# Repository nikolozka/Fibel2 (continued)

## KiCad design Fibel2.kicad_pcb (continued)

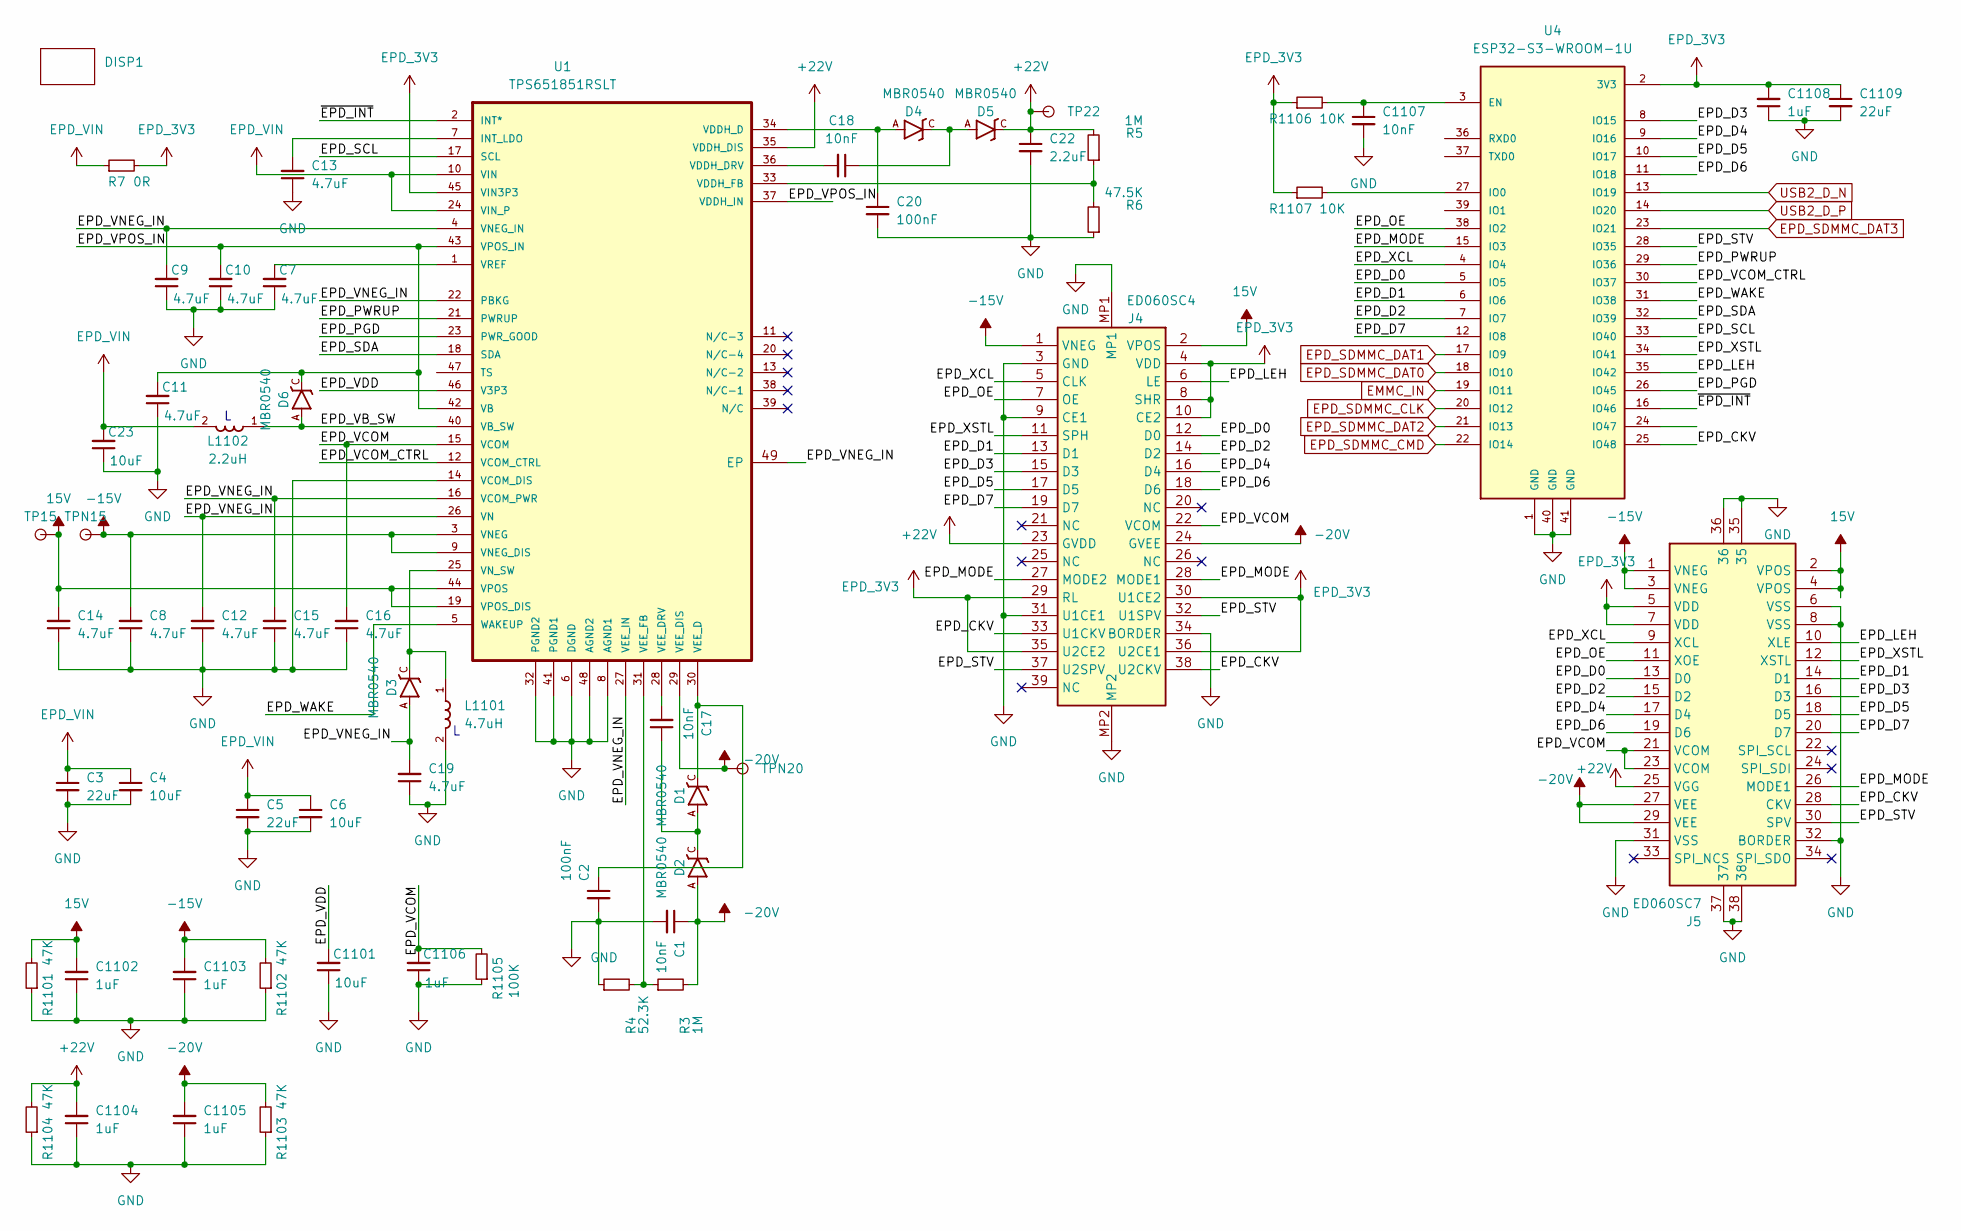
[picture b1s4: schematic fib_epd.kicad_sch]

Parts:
C1, C17, C18, C1107: 10nF; C_0402_1005Metric
C2, C20: 100nF; C_0402_1005Metric
C3, C5, C1109: 22uF; C_0805_2012Metric
C4, C6, C23: 10uF; C_0603_1608Metric
C7, C8, C9, C10, C11, C12, C13, C14, C15, C16, C19: 4.7uF; C_0402_1005Metric
C22: 2.2uF; C_0402_1005Metric
C1101: 10uF; C_0805_2012Metric
C1102, C1103, C1104, C1105, C1106, C1108: 1uF; C_0805_2012Metric
D1, D2, D3, D4, D5, D6: MBR0540; SOD-123
DISP1: 7.8 EInk
J4: ED060SC4; Mouser Part Number 798-FH26W39S03SHW60
J5: ED060SC7; Mouser Part Number 769-AXT334124
L1101: 4.7uH; IND_LQH5BPB4R7NT0L
L1102: 2.2uH; IND_LQH44PN4R7MP0L
R3, R5: 1M; R_0402_1005Metric
R4: 52.3K; R_0402_1005Metric
R6: 47.5K; R_0402_1005Metric
R7: 0R; R_0603_1608Metric
R1101, R1102, R1103, R1104: 47K; R_0402_1005Metric
R1105: 100K; R_0402_1005Metric
R1106, R1107: 10K; R_0402_1005Metric
TP15, TP22: TestPoint; TestPoint_Pad_D1.0mm
TPN15, TPN20: TestPoint; TestPoint_Pad_D1.0mm
U1: TPS651851RSLT; IC_TPS651851
U4: ESP32-S3-WROOM-1U; XCVR_ESP32-S3-WROOM-1U

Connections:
15V: C14.2, C1102.2, J4.2 (VPOS), J5.2 (VPOS), J5.4 (VPOS), R1101.2, TP15.1, U1.19 (VPOS_DIS), U1.44 (VPOS)
+22V: C22.1, C1104.2, D5.C, J4.23 (GVDD), J5.25 (VGG), R5.2, R1104.2, TP22.1, U1.35 (VDDH_DIS)
-15V: C8.2, C1103.2, J4.1 (VNEG), J5.1 (VNEG), J5.3 (VNEG), R1102.2, TPN15.1, U1.3 (VNEG), U1.9 (VNEG_DIS)
-20V: C1.1, C1105.2, D2.A, J4.24 (GVEE), J5.27 (VEE), J5.29 (VEE), R3.2, R1103.2, TPN20.1, U1.29 (VEE_DIS)
/EPD/EPD_CKV: J4.33 (U1CKV), J4.38 (U2CKV), J5.28 (CKV), U4.25 (IO48)
/EPD/EPD_D0: J4.12 (D0), J5.13 (D0), U4.5 (IO5)
/EPD/EPD_D1: J4.13 (D1), J5.14 (D1), U4.6 (IO6)
/EPD/EPD_D2: J4.14 (D2), J5.15 (D2), U4.7 (IO7)
/EPD/EPD_D3: J4.15 (D3), J5.16 (D3), U4.8 (IO15)
/EPD/EPD_D4: J4.16 (D4), J5.17 (D4), U4.9 (IO16)
/EPD/EPD_D5: J4.17 (D5), J5.18 (D5), U4.10 (IO17)
/EPD/EPD_D6: J4.18 (D6), J5.19 (D6), U4.11 (IO18)
/EPD/EPD_D7: J4.19 (D7), J5.20 (D7), U4.12 (IO8)
/EPD/EPD_LEH: J4.6 (LE), J5.10 (XLE), U4.35 (IO42)
/EPD/EPD_MODE: J4.27 (MODE2), J4.28 (MODE1), J5.26 (MODE1), U4.15 (IO3)
/EPD/EPD_OE: J4.7 (OE), J5.11 (XOE), U4.38 (IO2)
/EPD/EPD_PGD: U1.23 (PWR_GOOD), U4.26 (IO45)
/EPD/EPD_PWRUP: U1.21 (PWRUP), U4.29 (IO36)
/EPD/EPD_SCL: U1.17 (SCL), U4.33 (IO40)
/EPD/EPD_SDA: U1.18 (SDA), U4.32 (IO39)
/EPD/EPD_STV: J4.32 (U1SPV), J4.37 (U2SPV), J5.30 (SPV), U4.28 (IO35)
/EPD/EPD_VB_SW: D6.A, L1102.1, U1.40 (VB_SW)
/EPD/EPD_VCOM: C16.2, C1106.2, J4.22 (VCOM), J5.21 (VCOM), J5.23 (VCOM), R1105.2, U1.15 (VCOM)
/EPD/EPD_VCOM_CTRL: U1.12 (VCOM_CTRL), U4.30 (IO37)
/EPD/EPD_VDD: C1101.2, U1.46 (V3P3)
/EPD/EPD_VNEG_IN: C9.2, C12.2, C15.2, C19.2, D3.A, U1.4 (VNEG_IN), U1.16 (VCOM_PWR), U1.22 (PBKG), U1.26 (VN), U1.27 (VEE_IN), U1.49 (EP)
/EPD/EPD_VPOS_IN: C10.2, C11.2, D6.C, U1.37 (VDDH_IN), U1.42 (VB), U1.43 (VPOS_IN)
/EPD/EPD_WAKE: U1.5 (WAKEUP), U4.31 (IO38)
/EPD/EPD_XCL: J4.5 (CLK), J5.9 (XCL), U4.4 (IO4)
/EPD/EPD_XSTL: J4.11 (SPH), J5.12 (XSTL), U4.34 (IO41)
/EPD/~EPD_INT: U1.2 (INT*), U4.16 (IO46)
EMMC_IN: U4.19 (IO11); also elsewhere on the board
EPD_3V3: C1108.2, C1109.1, J4.4 (VDD), J4.8 (SHR), J4.10 (CE2), J4.29 (RL), J4.30 (U1CE2), J4.35 (U2CE2), J4.36 (U2CE1), J5.5 (VDD), J5.7 (VDD), R7.2, R1106.1, R1107.1, U1.45 (VIN3P3), U4.2 (3V3); also elsewhere on the board
EPD_SDMMC_CLK: U4.20 (IO12); also elsewhere on the board
EPD_SDMMC_CMD: U4.22 (IO14); also elsewhere on the board
EPD_SDMMC_DAT0: U4.18 (IO10); also elsewhere on the board
EPD_SDMMC_DAT1: U4.17 (IO9); also elsewhere on the board
EPD_SDMMC_DAT2: U4.21 (IO13); also elsewhere on the board
EPD_SDMMC_DAT3: U4.23 (IO21); also elsewhere on the board
EPD_VIN: C3.1, C4.1, C5.1, C6.1, C23.2, L1102.2, R7.1, U1.10 (VIN), U1.24 (VIN_P)
GND: C1.2, C2.2, C3.2, C4.2, C5.2, C6.2, C7.1, C8.1, C9.1, C10.1, C11.1, C12.1, C13.1, C14.1, C15.1, C16.1, C19.1, C20.2, C22.2, C23.1, C1101.1, C1102.1, C1103.1, C1104.1, C1105.1, C1106.1, C1107.2, C1108.1, C1109.2, J4.3 (GND), J4.9 (CE1), J4.31 (U1CE1), J4.34 (BORDER), J4.MP1, J4.MP2, J5.6 (VSS), J5.8 (VSS), J5.31 (VSS), J5.32 (BORDER), J5.35, J5.36, J5.37, J5.38, L1101.2, R4.1, R6.1, R1101.1, R1102.1, R1103.1, R1104.1, R1105.1, U1.6 (DGND), U1.8 (AGND1), U1.14 (VCOM_DIS), U1.32 (PGND2), U1.41 (PGND1), U1.48 (AGND2), U4.1 (GND), U4.40 (GND), U4.41 (GND); also elsewhere on the board
unnamed: C17.1, D1.A, D2.C
unnamed: C18.1, D4.C, D5.A
unnamed: C13.2, U1.7 (INT_LDO)
unnamed: C20.1, D4.A, U1.34 (VDDH_D)
unnamed: C18.2, U1.36 (VDDH_DRV)
unnamed: R5.1, R6.2, U1.33 (VDDH_FB)
unnamed: C2.1, D1.C, U1.30 (VEE_D)
unnamed: C17.2, U1.28 (VEE_DRV)
unnamed: R3.1, R4.2, U1.31 (VEE_FB)
unnamed: D3.C, L1101.1, U1.25 (VN_SW)
unnamed: C7.2, U1.1 (VREF)
unnamed: C1107.1, R1106.2, U4.3 (EN)
unnamed: R1107.2, U4.27 (IO0)
USB2_D_N: U4.13 (IO19); also elsewhere on the board
USB2_D_P: U4.14 (IO20); also elsewhere on the board

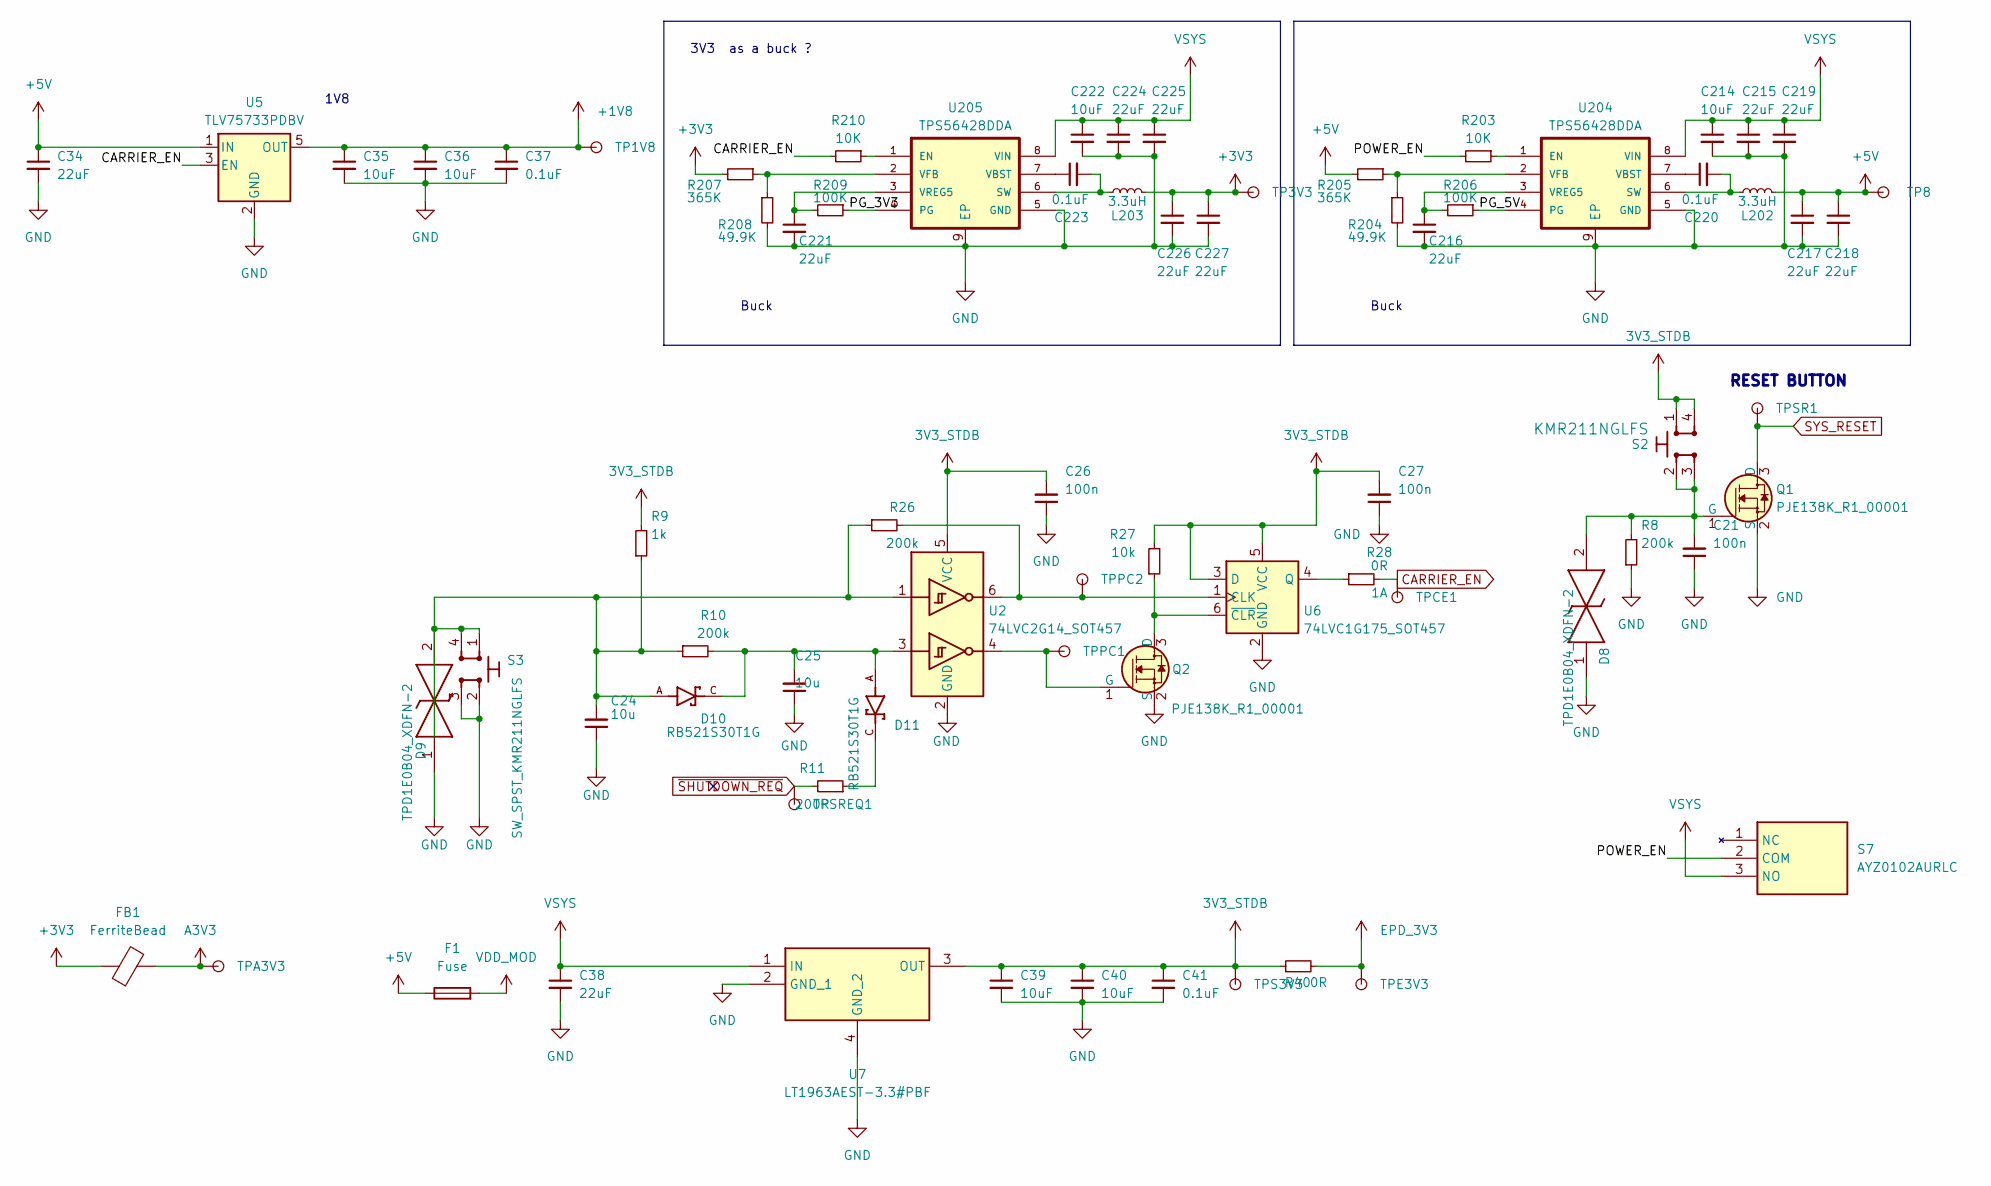
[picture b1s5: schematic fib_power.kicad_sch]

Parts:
C21, C26, C27: C_Small_Rota; C_0402_1005Metric; Voltage 50V; MPN GRM155R61H104KE14D
C24, C25: C_Small_Rota; C_0402_1005Metric; MPN CC0402MRX5R5BB106
C34, C38, C215, C216, C218, C219, C221, C224, C225, C227: 22uF; C_0805_2012Metric
C35, C36, C39, C40, C214, C222: 10uF; C_0603_1608Metric
C37, C41, C220, C223: 0.1uF; C_0402_1005Metric
C217, C226: 22uF; C_0603_1608Metric
D8, D9: TPD1E0B04_XDFN-2; TPD1E0B04DPYT; MPN TPD1E0B04DPYR; Mouser Part Number 595-TPD1E0B04DPYT
D10, D11: RB521S30T1G; MPN RB521S30T1G
F1: Fuse; Fuse_1206
FB1: FerriteBead; Ferrite_1206
L202, L203: 3.3uH; L_Coilcraft_XAL4030-XXX
Q1, Q2: PJE138K_2; SOT-523; MPN PJE138K_R1_00001
R8, R10, R26: R_Small_Rota; R_0402_1005Metric; Tolerance 1%; MPN CR0402-FX-2003GLF
R9: R_Small_Rota; R_0402_1005Metric; Tolerance 1%; MPN CR0402-FX-1001GLF
R11: R_Small_Rota; R_0402_1005Metric; Tolerance 1%; MPN CR0402-FX-2000GLF
R27: R_Small_Rota; R_0402_1005Metric; Tolerance 1%; MPN CR0402-FX-1002GLF
R28: R_Small_Rota; R_0402_1005Metric; MPN ERJ2GE0R00X
R40: 0R; R_0603_1608Metric
R203, R210: 10K; R_0402_1005Metric
R204, R208: 49.9K; R_0402_1005Metric
R205, R207: 365K; R_0402_1005Metric
R206, R209: 100K; R_0402_1005Metric
S2, S3: SW_SPST_KMR211NGLFS; KMR211NGLFS; MPN KMR211NGLFS
S7: AYZ0102AURLC; Mouser Part Number 611-AYZ0102AURLC
TP1V8, TP3V3, TP8: TestPoint; TestPoint_Pad_D1.0mm
TPA3V3: TestPoint; TestPoint_Pad_D1.0mm
TPCE1: TestPoint; TestPoint_Pad_D1.0mm
TPE3V3: TestPoint; TestPoint_Pad_D1.0mm
TPPC1, TPPC2: TestPoint; TestPoint_Pad_D1.0mm
TPS3V3: TestPoint; TestPoint_Pad_D1.0mm
TPSR1: TestPoint; TestPoint_Pad_D1.0mm
TPSREQ1: TestPoint; TestPoint_Pad_D1.0mm
U2: 74LVC2G14_SOT457; SOT-23-6; MPN 74LVC2G14GV,125
U5: TLV75733PDBV; SOT-23-5
U6: 74LVC1G175_SOT457; SOT-23-6; MPN 74LVC1G175GV,125
U7: LT1963AEST-3.3#PBF; SOT230P700X180-4N; Mouser Part Number 584-1963AEST-3.3PBF
U204, U205: TPS56428DDA

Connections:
3V3_STDB: C26.2, C27.2, C39.1, C40.1, C41.1, R9.2, R27.2, R40.1, S2.1, S2.4, TPS3V3.1, U2.5 (VCC), U6.3 (D), U6.5 (VCC), U7.3 (OUT); also elsewhere on the board
+1V8: C35.1, C36.1, C37.1, TP1V8.1, U5.5 (OUT); also elsewhere on the board
+3V3: C226.1, C227.1, FB1.1, L203.2, R207.2, TP3V3.1; also elsewhere on the board
+5V: C34.1, C217.1, C218.1, F1.1, L202.2, R205.2, TP8.1, U5.1 (IN); also elsewhere on the board
/Power/PG_3V3: R209.1, U205.4 (PG)
/Power/PG_5V: R206.1, U204.4 (PG)
/Power/POWER_EN: R203.2, S7.2 (COM)
A3V3: FB1.2, TPA3V3.1; also elsewhere on the board
CARRIER_EN: R28.2, R210.2, TPCE1.1, U5.3 (EN); also elsewhere on the board
EPD_3V3: R40.2, TPE3V3.1; also elsewhere on the board
GND: C21.1, C24.1, C25.1, C26.1, C27.1, C34.2, C35.2, C36.2, C37.2, C38.2, C39.2, C40.2, C41.2, C214.2, C215.2, C216.2, C217.2, C218.2, C219.2, C221.2, C222.2, C224.2, C225.2, C226.2, C227.2, D8.1, D9.1, Q1.2 (S), Q2.2 (S), R8.1, R204.2, R208.2, S3.2, S3.3, U2.2 (GND), U5.2 (GND), U6.2 (GND), U7.2 (GND_1), U7.4 (GND_2), U204.5 (GND), U204.9 (EP), U205.5 (GND), U205.9 (EP); also elsewhere on the board
unnamed: C24.2, D9.2, D10.A, R9.1, R10.1, R26.1, S3.1, S3.4, U2.1
unnamed: C25.2, D10.C, D11.A, R10.2, U2.3
unnamed: D11.C, R11.1
unnamed: C21.2, D8.2, Q1.1 (G), R8.2, S2.2, S2.3
unnamed: Q2.3 (D), R27.1, U6.6 (~CLR)
unnamed: Q2.1 (G), TPPC1.1, U2.4
unnamed: R26.2, TPPC2.1, U2.6, U6.1 (CLK)
unnamed: R28.1, U6.4 (Q)
unnamed: R203.1, U204.1 (EN)
unnamed: C220.2, L202.1, U204.6 (SW)
unnamed: C220.1, U204.7 (VBST)
unnamed: R204.1, R205.1, U204.2 (VFB)
unnamed: C216.1, R206.2, U204.3 (VREG5)
unnamed: R210.1, U205.1 (EN)
unnamed: C223.2, L203.1, U205.6 (SW)
unnamed: C223.1, U205.7 (VBST)
unnamed: R207.1, R208.1, U205.2 (VFB)
unnamed: C221.1, R209.2, U205.3 (VREG5)
SYS_RESET: Q1.3 (D), TPSR1.1; also elsewhere on the board
VDD_MOD: F1.2; also elsewhere on the board
VSYS: C38.1, C214.1, C215.1, C219.1, C222.1, C224.1, C225.1, S7.3 (NO), U7.1 (IN), U204.8 (VIN), U205.8 (VIN); also elsewhere on the board
~SHUTDOWN_REQ: R11.2, TPSREQ1.1; also elsewhere on the board

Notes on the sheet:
Buck
3V3 as a buck ?
1V8
RESET BUTTON

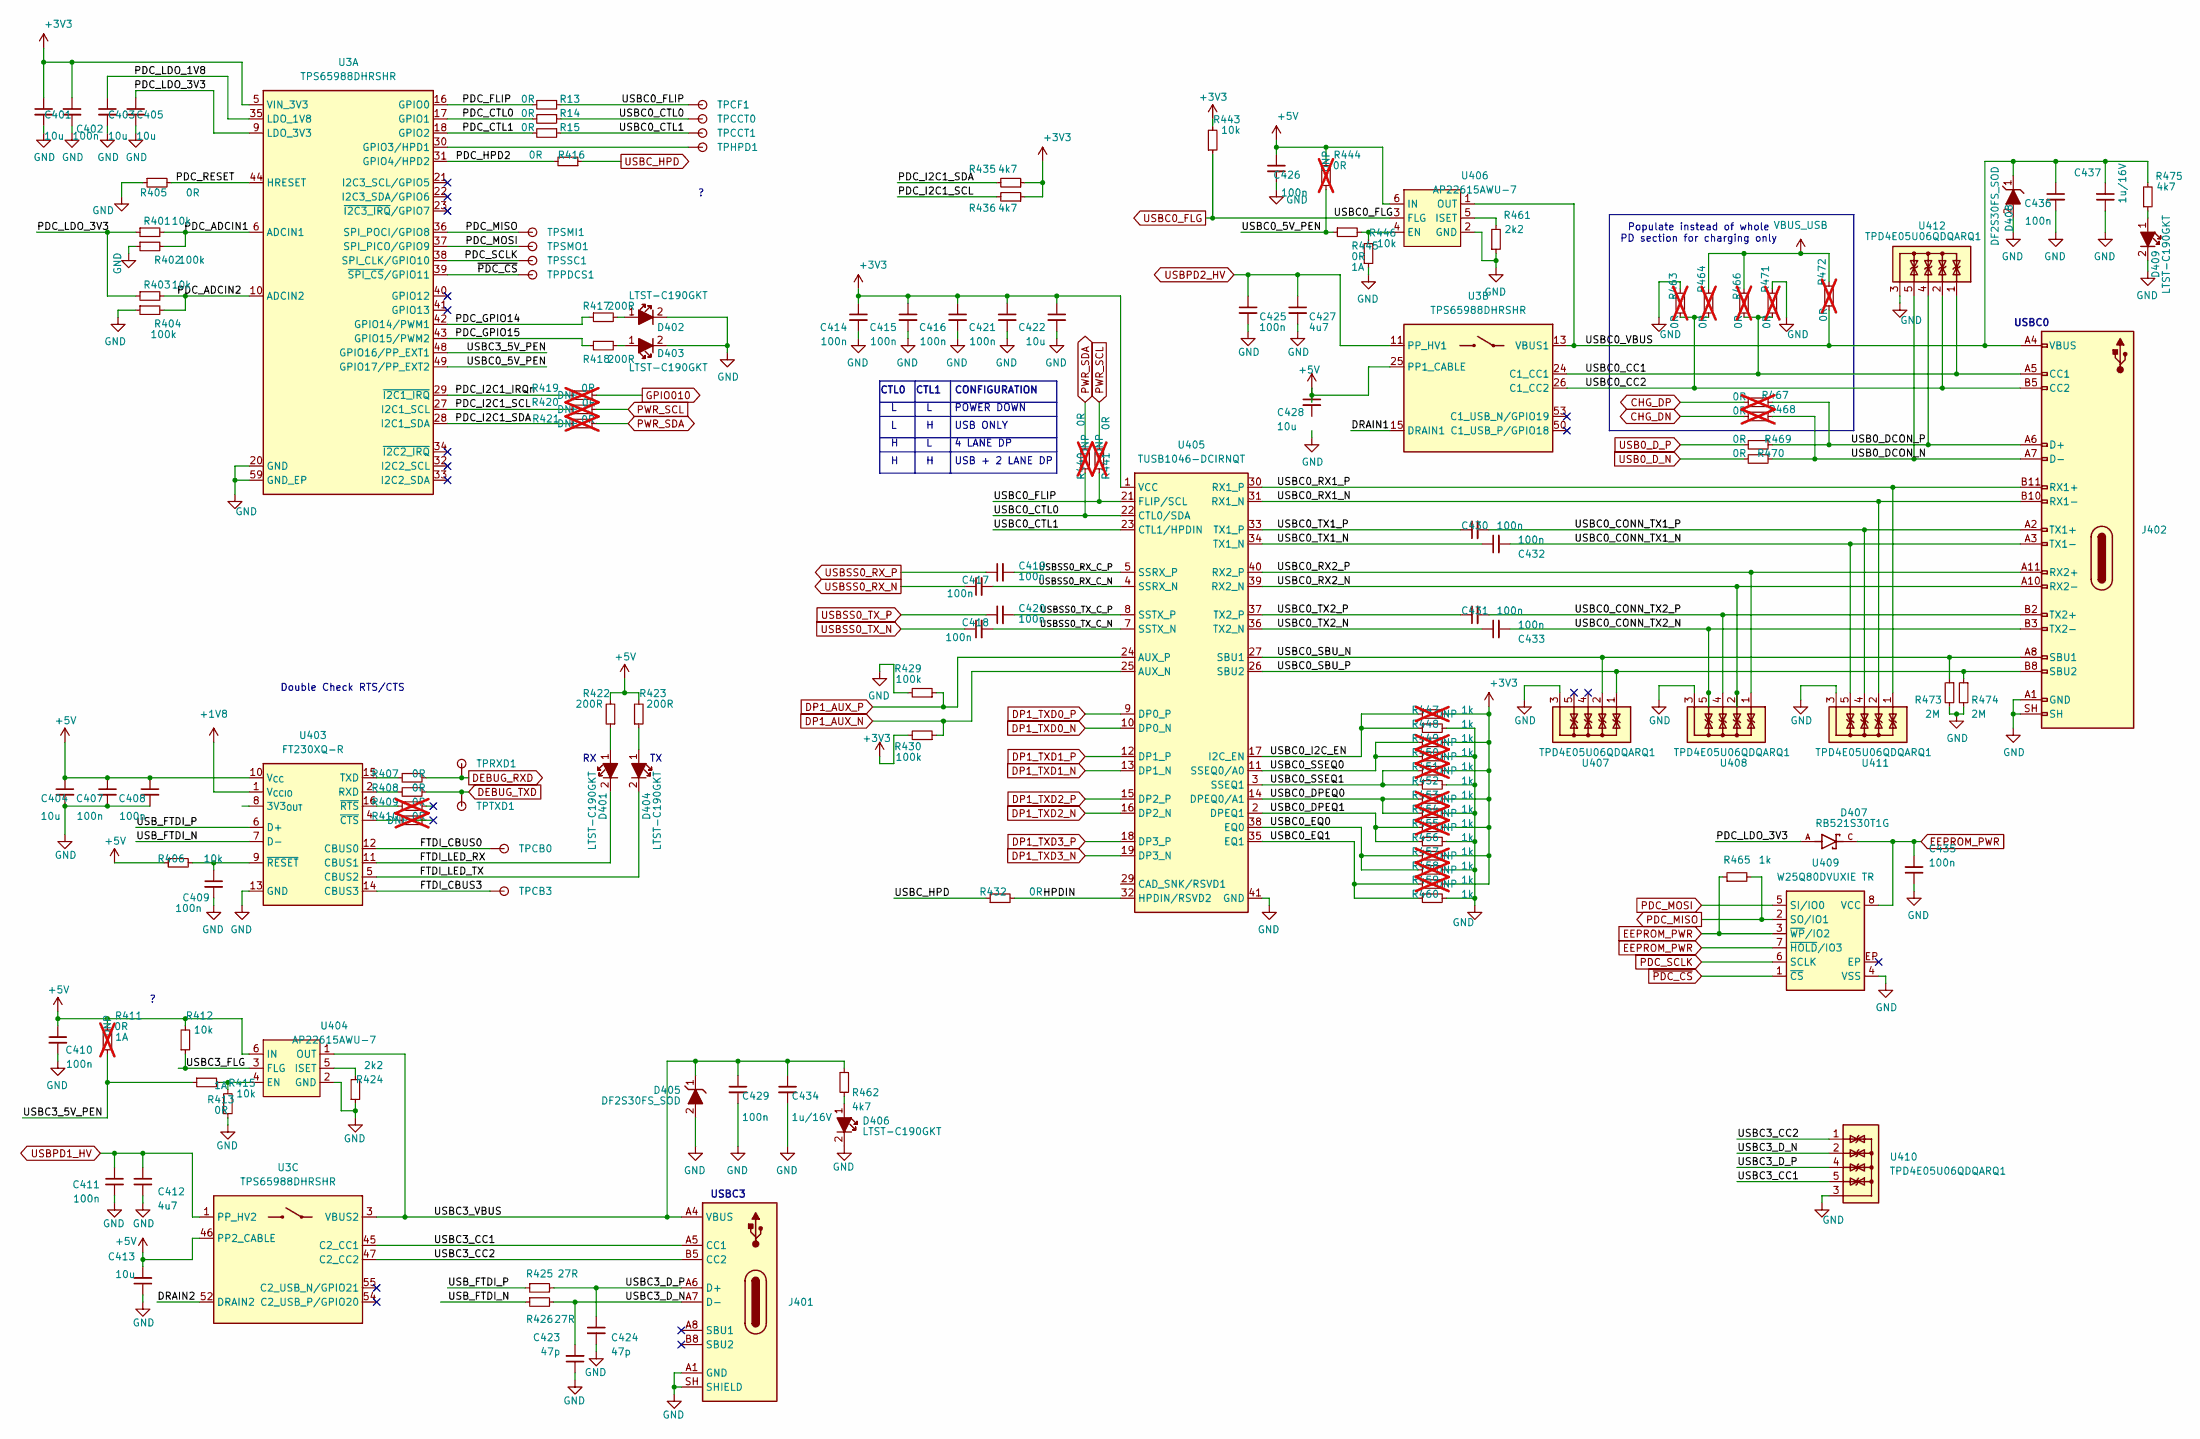
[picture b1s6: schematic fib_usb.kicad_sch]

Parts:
C401, C403, C404, C405, C413, C422, C428: 10uF; C_0603_1608Metric; MPN CC0402MRX5R5BB106
C402, C407, C408, C409, C410, C411, C414, C415, C416, C417, C418, C419, C420, C421, C425, C426, C429, C430, C431, C432, C433, C435, C436: 100nF; C_0402_1005Metric; Voltage 50V; MPN GRM155R61H104KE14D
C412, C427: 4.7uF; C_0402_1005Metric; Voltage 25V; MPN GRM155C61E475ME15J
C423, C424: 47pF; C_0402_1005Metric; MPN GRM1555C1E470JA01D
C434, C437: 1uF 16V; C_0603_1608Metric; MPN C0402C105M4PACTU
D401, D402, D403, D404, D406, D409: LED_G_0603_LTST-C190GKT; LED_0603_1608Metric; MPN LTST-C190GKT
D405, D408: DF2S30FS_SOD; D_SOD-923; MPN DF2S30FS
D407: RB521S30T1G; MPN RB521S30T1G
J401: USB-C_USB4105-GF-A; USB-C_GCT_USB4105-GF-A; MPN USB4105-GF-A
J402: Conn_USB-C_WE_632723300011; MPN 632723300011
R13, R14, R15, R469, R470: 0R; R_0402_1005Metric
R401, R403, R406, R412, R415, R443, R446: 10K; R_0402_1005Metric; Tolerance 1%; MPN CR0402-FX-1002GLF
R402, R404, R429, R430: 100K; R_0402_1005Metric; Tolerance 1%; MPN CR0402-FX-1003GLF
R405, R407, R408, R413, R416, R432, R445: 0R; R_0402_1005Metric; MPN ERJ2GE0R00X
R409, R410, R411, R419, R420, R421, R440, R441, R444: 0R; R_0402_1005Metric; MPN ERJ2GE0R00X; not fitted
R417, R418, R422, R423: 200R; R_0402_1005Metric; Tolerance 1%; MPN CR0402-FX-2000GLF
R424, R461: 2.2K; R_0402_1005Metric; Tolerance 1%; MPN CR0402-FX-2201GLF
R425, R426: 27R; R_0402_1005Metric; Tolerance 1%; MPN CR0402-FX-27R0GLF
R435, R436, R462, R475: 4.7K; R_0402_1005Metric; Tolerance 1%; MPN CR0402-FX-4701GLF
R447, R449, R450, R451, R453, R454, R455, R457, R458, R459: 2K; R_0402_1005Metric; Tolerance 1%; MPN CR0402-FX-1001GLF; not fitted
R448, R452, R456, R460, R465: 1K; R_0402_1005Metric; Tolerance 1%; MPN CR0402-FX-1001GLF
R463, R464, R466, R467, R468, R471: 0R; R_0402_1005Metric; not fitted
R472: 0R; R_0603_1608Metric; not fitted
R473, R474: 3M; R_0402_1005Metric; Tolerance 1%; MPN CR0402-FX-2004GLF
TPCB0, TPCB3: TestPoint; TestPoint_Pad_D1.0mm
TPCCT0, TPCCT1: TestPoint; TestPoint_Pad_D1.0mm
TPCF1: TestPoint; TestPoint_Pad_D1.0mm
TPHPD1: TestPoint; TestPoint_Pad_D1.0mm
TPPDCS1: TestPoint; TestPoint_Pad_D1.0mm
TPRXD1: TestPoint; TestPoint_Pad_D1.0mm
TPSMI1: TestPoint; TestPoint_Pad_D1.0mm
TPSMO1: TestPoint; TestPoint_Pad_D1.0mm
TPSSC1: TestPoint; TestPoint_Pad_D1.0mm
TPTXD1: TestPoint; TestPoint_Pad_D1.0mm
U3: TPS65988DHRSHR; IC_TPS65987DDHRSHR; MPN TPS65988DHRSHR
U403: FT230X_QFN; QFN-16_1EP_4x4mm_P0.65mm; MPN FT230XQ-R
U404, U406: AP22615_1; TSOT23-6; MPN AP22615AWU-7
U405: TUSB1046-DCIRNQ; WQFN-40_1EP_6x3mm_Pitch0.4mm_EP4.7x2.7mm; MPN TUSB1046-DCIRNQT
U407, U408, U410, U411, U412: TPD4E05U06QDQARQ1; USON-10_2.5x1mm_P0.5mm; MPN TPD4E05U06QDQARQ1
U409: W25Q80DV_USON; USON-8_2x3mm_P0.5mm; MPN W25Q80DVUXIE TR

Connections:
+1V8: U403.1 (V_{CCIO}); also elsewhere on the board
+3V3: C401.1, C402.1, C414.1, C415.1, C416.1, C421.1, C422.1, R430.2, R435.1, R436.1, R443.2, R447.2, R449.2, R451.2, R453.2, R455.2, R457.2, R459.2, U3.5 (VIN_3V3), U405.1 (VCC), U405.6 (VCC), U405.20 (VCC), U405.28 (VCC); also elsewhere on the board
+5V: C404.1, C407.1, C408.1, C410.1, C413.2, C426.1, C428.1, R406.1, R411.2, R412.2, R422.2, R423.2, R444.2, U3.25 (PP1_CABLE), U3.46 (PP2_CABLE), U403.10 (V_{CC}), U404.6 (IN), U406.6 (IN); also elsewhere on the board
/USB/DRAIN1: U3.8 (DRAIN1), U3.15 (DRAIN1), U3.19 (DRAIN1), U3.58 (DRAIN1)
/USB/DRAIN2: U3.7 (DRAIN2), U3.52 (DRAIN2), U3.56 (DRAIN2), U3.57 (DRAIN2)
/USB/FTDI_CBUS0: TPCB0.1, U403.12 (CBUS0)
/USB/FTDI_CBUS3: TPCB3.1, U403.14 (CBUS3)
/USB/FTDI_LED_RX: D401.2, U403.11 (CBUS1)
/USB/FTDI_LED_TX: D404.2, U403.5 (CBUS2)
/USB/HPDIN: R432.2, U405.32 (HPDIN/RSVD2)
/USB/PDC_ADCIN1: R401.2, R402.2, U3.6 (ADCIN1)
/USB/PDC_ADCIN2: R403.2, R404.2, U3.10 (ADCIN2)
/USB/PDC_CTL0: R14.2, U3.17 (GPIO1)
/USB/PDC_CTL1: R15.2, U3.18 (GPIO2)
/USB/PDC_FLIP: R13.2, U3.16 (GPIO0)
/USB/PDC_GPIO14: R417.1, U3.42 (GPIO14/PWM1)
/USB/PDC_GPIO15: R418.1, U3.43 (GPIO15/PWM2)
/USB/PDC_HPD2: R416.2, U3.31 (GPIO4/HPD2)
/USB/PDC_I2C1_IRQn: R419.2, U3.29 (~I2C1_IRQ)
/USB/PDC_I2C1_SCL: R420.2, R436.2, U3.27 (I2C1_SCL)
/USB/PDC_I2C1_SDA: R421.2, R435.2, U3.28 (I2C1_SDA)
/USB/PDC_LDO_1V8: C403.1, U3.35 (LDO_1V8)
/USB/PDC_LDO_3V3: C405.1, D407.A, R401.1, R403.1, U3.9 (LDO_3V3)
/USB/PDC_RESET: R405.2, U3.44 (HRESET)
/USB/USB0_DCON_N: J402.A7 (D-), J402.B7 (D-), R468.1, R470.1, U412.5, U412.6
/USB/USB0_DCON_P: J402.A6 (D+), J402.B6 (D+), R467.1, R469.1, U412.4, U412.7
/USB/USBC0_5V_PEN: R444.1, R445.1, U3.49 (GPIO17/PP_EXT2)
/USB/USBC0_CC1: J402.A5 (CC1), R466.2, R471.2, U3.24 (C1_CC1), U412.1, U412.10
/USB/USBC0_CC2: J402.B5 (CC2), R463.2, R464.2, U3.26 (C1_CC2), U412.2, U412.9
/USB/USBC0_CONN_TX1_N: C432.2, J402.A3 (TX1-), U411.5, U411.6
/USB/USBC0_CONN_TX1_P: C430.2, J402.A2 (TX1+), U411.4, U411.7
/USB/USBC0_CONN_TX2_N: C433.2, J402.B3 (TX2-), U408.5, U408.6
/USB/USBC0_CONN_TX2_P: C431.2, J402.B2 (TX2+), U408.4, U408.7
/USB/USBC0_CTL0: R14.1, R440.1, TPCCT0.1, U405.22 (CTL0/SDA)
/USB/USBC0_CTL1: R15.1, TPCCT1.1, U405.23 (CTL1/HPDIN)
/USB/USBC0_DPEQ0: R453.1, R454.1, U405.14 (DPEQ0/A1)
/USB/USBC0_DPEQ1: R455.1, R456.1, U405.2 (DPEQ1)
/USB/USBC0_EQ0: R457.1, R458.1, U405.38 (EQ0)
/USB/USBC0_EQ1: R459.1, R460.1, U405.35 (EQ1)
/USB/USBC0_FLIP: R13.1, R441.1, TPCF1.1, U405.21 (FLIP/SCL)
/USB/USBC0_I2C_EN: R447.1, R448.1, U405.17 (I2C_EN)
/USB/USBC0_RX1_N: J402.B10 (RX1-), U405.31 (RX1_N), U411.2, U411.9
/USB/USBC0_RX1_P: J402.B11 (RX1+), U405.30 (RX1_P), U411.1, U411.10
/USB/USBC0_RX2_N: J402.A10 (RX2-), U405.39 (RX2_N), U408.2, U408.9
/USB/USBC0_RX2_P: J402.A11 (RX2+), U405.40 (RX2_P), U408.1, U408.10
/USB/USBC0_SBU_N: J402.A8 (SBU1), R473.1, U405.27 (SBU1), U407.2, U407.9
/USB/USBC0_SBU_P: J402.B8 (SBU2), R474.1, U405.26 (SBU2), U407.1, U407.10
/USB/USBC0_SSEQ0: R449.1, R450.1, U405.11 (SSEQ0/A0)
/USB/USBC0_SSEQ1: R451.1, R452.1, U405.3 (SSEQ1)
/USB/USBC0_TX1_N: C432.1, U405.34 (TX1_N)
/USB/USBC0_TX1_P: C430.1, U405.33 (TX1_P)
/USB/USBC0_TX2_N: C433.1, U405.36 (TX2_N)
/USB/USBC0_TX2_P: C431.1, U405.37 (TX2_P)
/USB/USBC0_VBUS: C436.1, C437.2, D408.1, J402.A4 (VBUS), J402.A9 (VBUS), J402.B4 (VBUS), J402.B9 (VBUS), R472.2, R475.2, U3.13 (VBUS1), U406.1 (OUT)
/USB/USBC3_5V_PEN: R411.1, R413.1, U3.48 (GPIO16/PP_EXT1)
/USB/USBC3_CC1: J401.A5 (CC1), U3.45 (C2_CC1), U410.5, U410.6
/USB/USBC3_CC2: J401.B5 (CC2), U3.47 (C2_CC2), U410.1, U410.10
/USB/USBC3_D_N: C423.2, J401.A7 (D-), J401.B7 (D-), R426.2, U410.2, U410.9
/USB/USBC3_D_P: C424.1, J401.A6 (D+), J401.B6 (D+), R425.2, U410.4, U410.7
/USB/USBC3_FLG: R412.1, U404.3 (FLG)
/USB/USBC3_VBUS: C429.1, C434.1, D405.1, J401.A4 (VBUS), J401.A9 (VBUS), J401.B4 (VBUS), J401.B9 (VBUS), R462.1, U3.3 (VBUS2), U404.1 (OUT)
/USB/USBSS0_RX_C_N: C417.2, U405.4 (SSRX_N)
/USB/USBSS0_RX_C_P: C419.2, U405.5 (SSRX_P)
/USB/USBSS0_TX_C_N: C418.2, U405.7 (SSTX_N)
/USB/USBSS0_TX_C_P: C420.2, U405.8 (SSTX_P)
/USB/USB_FTDI_N: R426.1, U403.7 (D-)
/USB/USB_FTDI_P: R425.1, U403.6 (D+)
CHG_DN: R468.2; also elsewhere on the board
CHG_DP: R467.2; also elsewhere on the board
DEBUG_RXD: R407.1, TPRXD1.1; also elsewhere on the board
DEBUG_TXD: R408.1, TPTXD1.1; also elsewhere on the board
DP1_AUX_N: R430.1, U405.25 (AUX_N); also elsewhere on the board
DP1_AUX_P: R429.1, U405.24 (AUX_P); also elsewhere on the board
DP1_TXD0_N: U405.10 (DP0_N); also elsewhere on the board
DP1_TXD0_P: U405.9 (DP0_P); also elsewhere on the board
DP1_TXD1_N: U405.13 (DP1_N); also elsewhere on the board
DP1_TXD1_P: U405.12 (DP1_P); also elsewhere on the board
DP1_TXD2_N: U405.16 (DP2_N); also elsewhere on the board
DP1_TXD2_P: U405.15 (DP2_P); also elsewhere on the board
DP1_TXD3_N: U405.19 (DP3_N); also elsewhere on the board
DP1_TXD3_P: U405.18 (DP3_P); also elsewhere on the board
EEPROM_PWR: C435.2, D407.C, R465.1, U409.3 (~WP/IO2), U409.7 (~HOLD/IO3), U409.8 (VCC)
GND: C401.2, C402.2, C403.2, C404.2, C405.2, C407.2, C408.2, C409.2, C410.2, C411.2, C412.2, C413.1, C414.2, C415.2, C416.2, C421.2, C422.2, C423.1, C424.2, C425.2, C426.2, C427.2, C429.2, C434.2, C435.1, C436.2, C437.1, D402.2, D403.2, D405.2, D406.2, D408.2, D409.2, J401.A1 (GND), J401.A12 (GND), J401.B1 (GND), J401.B12 (GND), J401.SH (SHIELD), J402.A1 (GND), J402.A12 (GND), J402.B1 (GND), J402.B12 (GND), J402.SH, R402.1, R404.1, R405.1, R415.1, R424.1, R429.2, R446.1, R448.2, R450.2, R452.2, R454.2, R456.2, R458.2, R460.2, R461.1, R463.1, R471.1, R473.2, R474.2, U3.20 (GND), U3.51 (GND), U3.59 (GND_EP), U403.3 (GND), U403.13 (GND), U403.17 (GND), U404.2 (GND), U405.41 (GND), U406.2 (GND), U407.3, U407.8, U408.3, U408.8, U409.4 (VSS), U410.3, U410.8, U411.3, U411.8, U412.3, U412.8; also elsewhere on the board
GPIO010: R419.1; also elsewhere on the board
unnamed: D401.1, R422.1
unnamed: D402.1, R417.2
unnamed: D403.1, R418.2
unnamed: D404.1, R423.1
unnamed: D406.1, R462.2
unnamed: D409.1, R475.1
unnamed: TPHPD1.1, U3.30 (GPIO3/HPD1)
unnamed: R408.2, U403.2 (RXD)
unnamed: R407.2, U403.15 (TXD)
unnamed: R410.2, U403.4 (~CTS)
unnamed: C409.1, R406.2, U403.9 (~RESET)
unnamed: R409.2, U403.16 (~RTS)
unnamed: R413.2, R415.2, U404.4 (EN)
unnamed: R424.2, U404.5 (ISET)
unnamed: R445.2, R446.2, U406.4 (EN)
unnamed: R461.2, U406.5 (ISET)
PDC_MISO: R465.2, TPSMI1.1, U3.36 (SPI_POCI/GPIO8), U409.2 (SO/IO1)
PDC_MOSI: TPSMO1.1, U3.37 (SPI_PICO/GPIO9), U409.5 (SI/IO0)
PDC_SCLK: TPSSC1.1, U3.38 (SPI_CLK/GPIO10), U409.6 (SCLK)
PWR_SCL: R420.1, R441.2; also elsewhere on the board
PWR_SDA: R421.1, R440.2; also elsewhere on the board
USB0_D_N: R470.2; also elsewhere on the board
USB0_D_P: R469.2; also elsewhere on the board
USBC0_FLG: R443.1, U406.3 (FLG)
USBC_HPD: R416.1, R432.1
USBPD1_HV: C411.1, C412.1, U3.1 (PP_HV2); also elsewhere on the board
USBPD2_HV: C425.1, C427.1, U3.11 (PP_HV1); also elsewhere on the board
USBSS0_RX_N: C417.1; also elsewhere on the board
USBSS0_RX_P: C419.1; also elsewhere on the board
USBSS0_TX_N: C418.1; also elsewhere on the board
USBSS0_TX_P: C420.1; also elsewhere on the board
VBUS_USB: R464.1, R466.1, R472.1; also elsewhere on the board
~PDC_CS: TPPDCS1.1, U3.39 (~SPI_CS/GPIO11), U409.1 (~CS)

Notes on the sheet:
Double Check RTS/CTS
USBC0
Populate instead of whole PD section for charging only
USB + 2 LANE DP
POWER DOWN
4 LANE DP
USBC3
CTL1
CTL0
USB ONLY
CONFIGURATION
